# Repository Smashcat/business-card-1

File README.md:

# business-card-1
LED business card with a 15 x 5 LED matrix. Using ATMega168PB microcontroller, and real time clock chip. Powered by single CR2032 coin cell. All SMD parts, so if you're having PCBs made with this design I'd strongly suggest also buying a stencil to make it a LOT easier to solder! In my code I'm using deep sleep, with the button triggering a pin change interrupt to wake it. I use a 10khz timer interrupt to multiplexthe LEDs, which gives a good brightness, and allows for at least 16 greyscale levels.

Note that I'm using 100ohm resistors for the rows - this allows you to run the card at both 3v and 5v - however if you're only using 3v, I'd suggest lowering the resistor value to 50ohms, to increase brightness. 3D printing an acrylic cover to diffuse the LEDs would be a nice touch too! If I get a design done I'll add it here!

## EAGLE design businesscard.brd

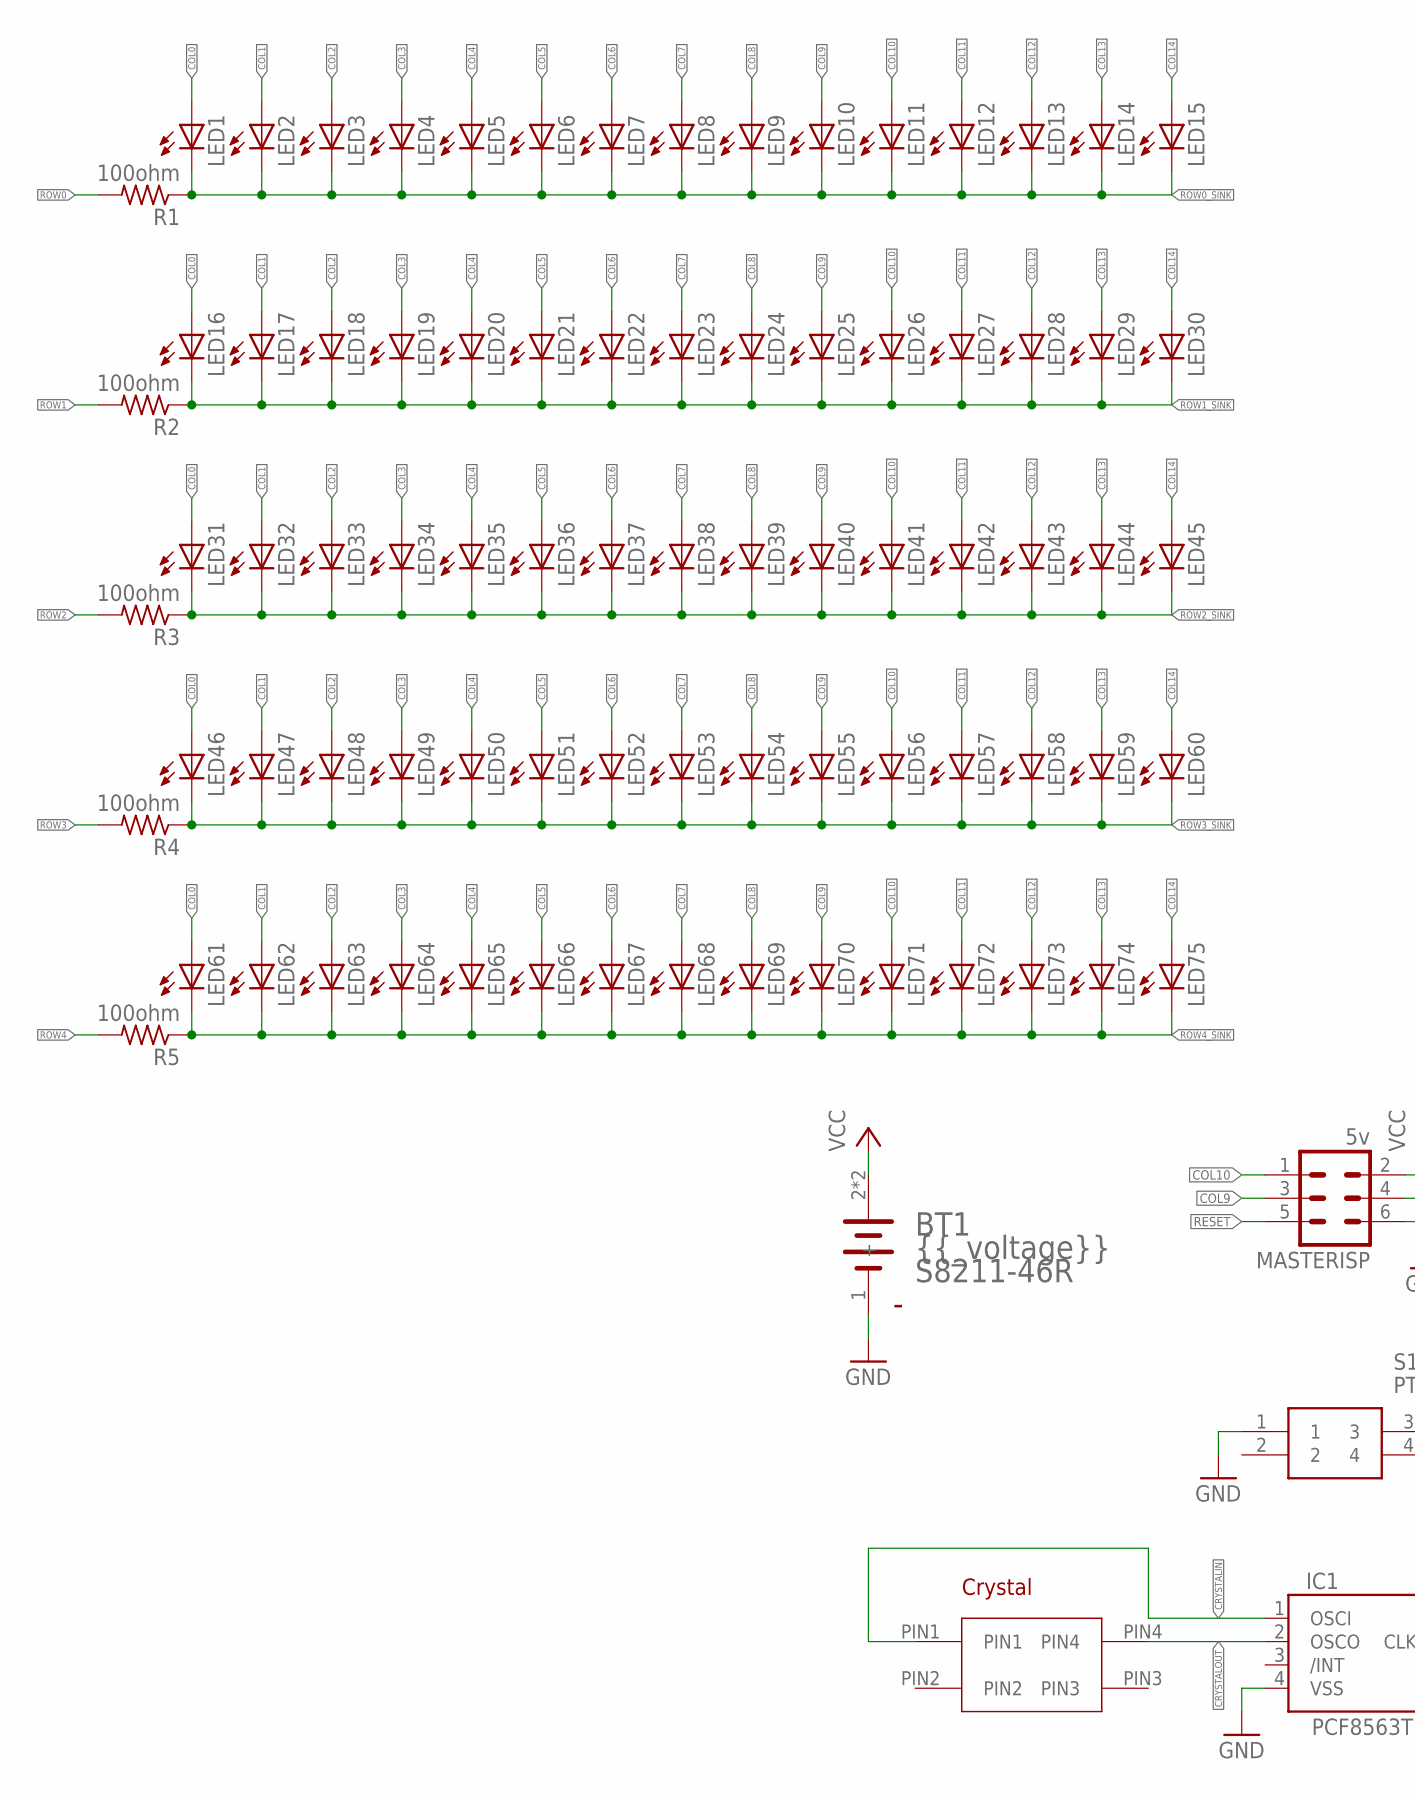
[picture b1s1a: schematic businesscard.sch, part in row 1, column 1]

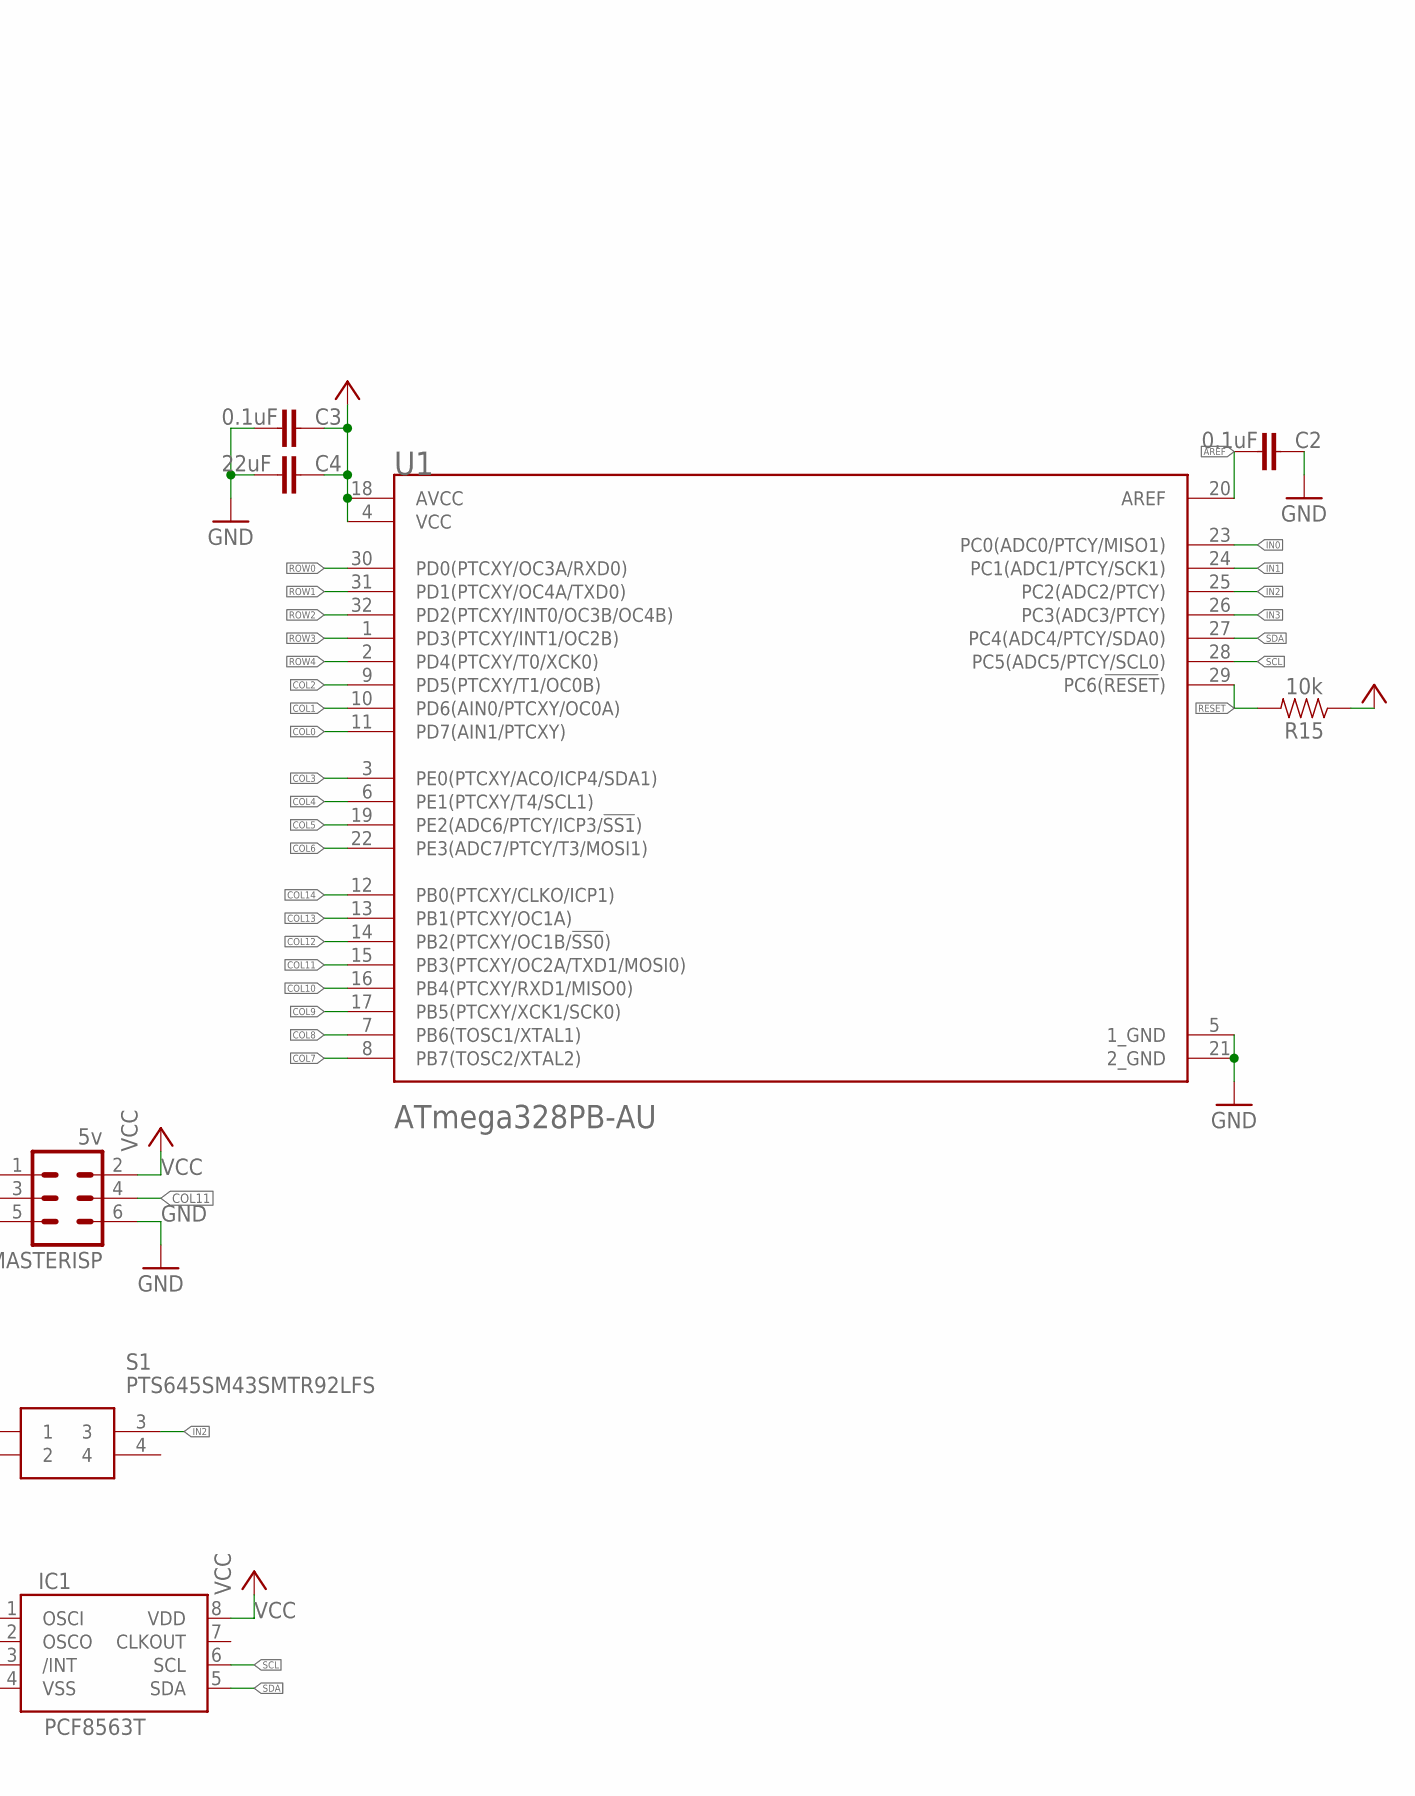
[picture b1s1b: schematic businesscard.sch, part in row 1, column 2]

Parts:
BT1: 3v; HARWIN_S8211-46R_0
C2: 0.1uF; C0603
C3: 0.1uF; 0603
C4: 22uF; C0603
IC1: PCF8563T; SO8
LED1, LED2, LED3, LED4, LED5, LED6, LED7, LED8, LED9, LED10, LED11, LED12, LED13, LED14, LED15, LED16, LED17, LED18, LED19, LED20, LED21, LED22, LED23, LED24, LED25, LED26, LED27, LED28, LED29, LED30, LED31, LED32, LED33, LED34, LED35, LED36, LED37, LED38, LED39, LED40, LED41, LED42, LED43, LED44, LED45, LED46, LED47, LED48, LED49, LED50, LED51, LED52, LED53, LED54, LED55, LED56, LED57, LED58, LED59, LED60, LED61, LED62, LED63, LED64, LED65, LED66, LED67, LED68, LED69, LED70, LED71, LED72, LED73, LED74, LED75: LEDCHIPLED_0805; CHIPLED_0805
MASTERISP: 5v; MA03-2
R1, R2, R3, R4, R5: 100ohm; R0603
R15: 10k; 0603
S1: PTS645SM43SMTR92LFS; PTS645(SMT)
U1: MICROCHIP_ATMEGA328PB-AUMICROCHIP_ATMEGA328PB-AU_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; MICROCHIP_ATMEGA328PB-AU_0
U$1: 32.768_SMD_CRYSTAL

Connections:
AREF: C2.2, U1.20 (AREF)
COL0: LED1.A, LED16.A, LED31.A, LED46.A, LED61.A, U1.11 (PD7(AIN1/PTCXY))
COL1: LED2.A, LED17.A, LED32.A, LED47.A, LED62.A, U1.10 (PD6(AIN0/PTCXY/OC0A))
COL2: LED3.A, LED18.A, LED33.A, LED48.A, LED63.A, U1.9 (PD5(PTCXY/T1/OC0B))
COL3: LED4.A, LED19.A, LED34.A, LED49.A, LED64.A, U1.3 (PE0(PTCXY/ACO/ICP4/SDA1))
COL4: LED5.A, LED20.A, LED35.A, LED50.A, LED65.A, U1.6 (PE1(PTCXY/T4/SCL1))
COL5: LED6.A, LED21.A, LED36.A, LED51.A, LED66.A, U1.19 (PE2(ADC6/PTCY/ICP3/!SS1!))
COL6: LED7.A, LED22.A, LED37.A, LED52.A, LED67.A, U1.22 (PE3(ADC7/PTCY/T3/MOSI1))
COL7: LED8.A, LED23.A, LED38.A, LED53.A, LED68.A, U1.8 (PB7(TOSC2/XTAL2))
COL8: LED9.A, LED24.A, LED39.A, LED54.A, LED69.A, U1.7 (PB6(TOSC1/XTAL1))
COL9: LED10.A, LED25.A, LED40.A, LED55.A, LED70.A, MASTERISP.3, U1.17 (PB5(PTCXY/XCK1/SCK0))
COL10: LED11.A, LED26.A, LED41.A, LED56.A, LED71.A, MASTERISP.1, U1.16 (PB4(PTCXY/RXD1/MISO0))
COL11: LED12.A, LED27.A, LED42.A, LED57.A, LED72.A, MASTERISP.4, U1.15 (PB3(PTCXY/OC2A/TXD1/MOSI0))
COL12: LED13.A, LED28.A, LED43.A, LED58.A, LED73.A, U1.14 (PB2(PTCXY/OC1B/!SS0!))
COL13: LED14.A, LED29.A, LED44.A, LED59.A, LED74.A, U1.13 (PB1(PTCXY/OC1A))
COL14: LED15.A, LED30.A, LED45.A, LED60.A, LED75.A, U1.12 (PB0(PTCXY/CLKO/ICP1))
CRYSTALIN: IC1.1 (OSCI), U$1.PIN1
CRYSTALOUT: IC1.2 (OSCO), U$1.PIN4
GND: BT1.1 (-), C2.1, C3.2, C4.2, IC1.4 (VSS), MASTERISP.6, S1.1, U1.5 (1_GND), U1.21 (2_GND)
IN0: U1.23 (PC0(ADC0/PTCY/MISO1))
IN1: U1.24 (PC1(ADC1/PTCY/SCK1))
IN2: S1.3, U1.25 (PC2(ADC2/PTCY))
IN3: U1.26 (PC3(ADC3/PTCY))
RESET: MASTERISP.5, R15.2, U1.29 (PC6(!RESET!))
ROW0: R1.2, U1.30 (PD0(PTCXY/OC3A/RXD0))
ROW0_SINK: LED1.C, LED2.C, LED3.C, LED4.C, LED5.C, LED6.C, LED7.C, LED8.C, LED9.C, LED10.C, LED11.C, LED12.C, LED13.C, LED14.C, LED15.C, R1.1
ROW1: R2.2, U1.31 (PD1(PTCXY/OC4A/TXD0))
ROW1_SINK: LED16.C, LED17.C, LED18.C, LED19.C, LED20.C, LED21.C, LED22.C, LED23.C, LED24.C, LED25.C, LED26.C, LED27.C, LED28.C, LED29.C, LED30.C, R2.1
ROW2: R3.2, U1.32 (PD2(PTCXY/INT0/OC3B/OC4B))
ROW2_SINK: LED31.C, LED32.C, LED33.C, LED34.C, LED35.C, LED36.C, LED37.C, LED38.C, LED39.C, LED40.C, LED41.C, LED42.C, LED43.C, LED44.C, LED45.C, R3.1
ROW3: R4.2, U1.1 (PD3(PTCXY/INT1/OC2B))
ROW3_SINK: LED46.C, LED47.C, LED48.C, LED49.C, LED50.C, LED51.C, LED52.C, LED53.C, LED54.C, LED55.C, LED56.C, LED57.C, LED58.C, LED59.C, LED60.C, R4.1
ROW4: R5.2, U1.2 (PD4(PTCXY/T0/XCK0))
ROW4_SINK: LED61.C, LED62.C, LED63.C, LED64.C, LED65.C, LED66.C, LED67.C, LED68.C, LED69.C, LED70.C, LED71.C, LED72.C, LED73.C, LED74.C, LED75.C, R5.1
SCL: IC1.6 (SCL), U1.28 (PC5(ADC5/PTCY/SCL0))
SDA: IC1.5 (SDA), U1.27 (PC4(ADC4/PTCY/SDA0))
VCC: BT1.2 (+), BT1.2-2 (+), C3.1, C4.1, IC1.8 (VDD), MASTERISP.2, R15.1, U1.4 (VCC), U1.18 (AVCC)

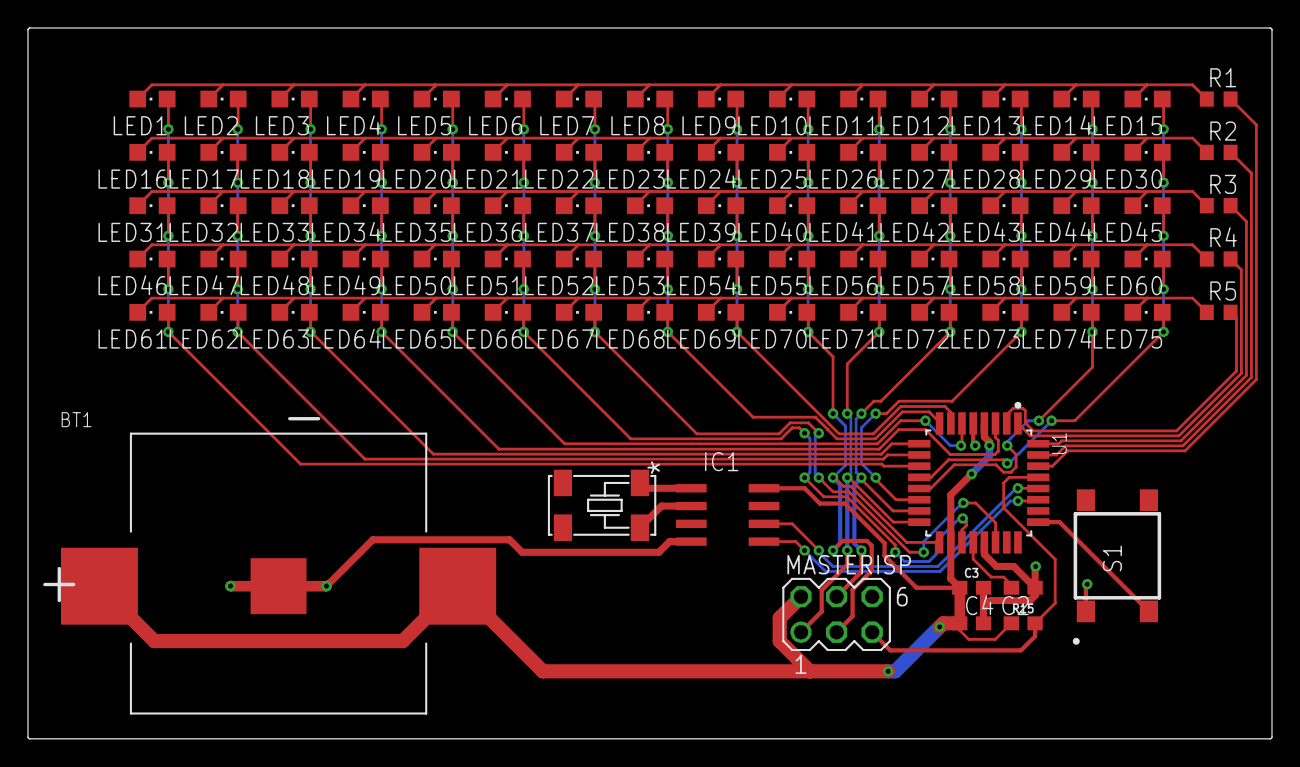
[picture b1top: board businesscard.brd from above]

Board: 2 copper layers, 88.9 x 50.8 mm, 90 parts (0 on the bottom side), 34 nets.

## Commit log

2019-02-04 Added schematic and gerbers

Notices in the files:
parts and their libraries:
SparkFun-Capacitors: Licensing: Creative Commons ShareAlike 4.0 International - https://creativecommons.org/licenses/by-sa/4.0
